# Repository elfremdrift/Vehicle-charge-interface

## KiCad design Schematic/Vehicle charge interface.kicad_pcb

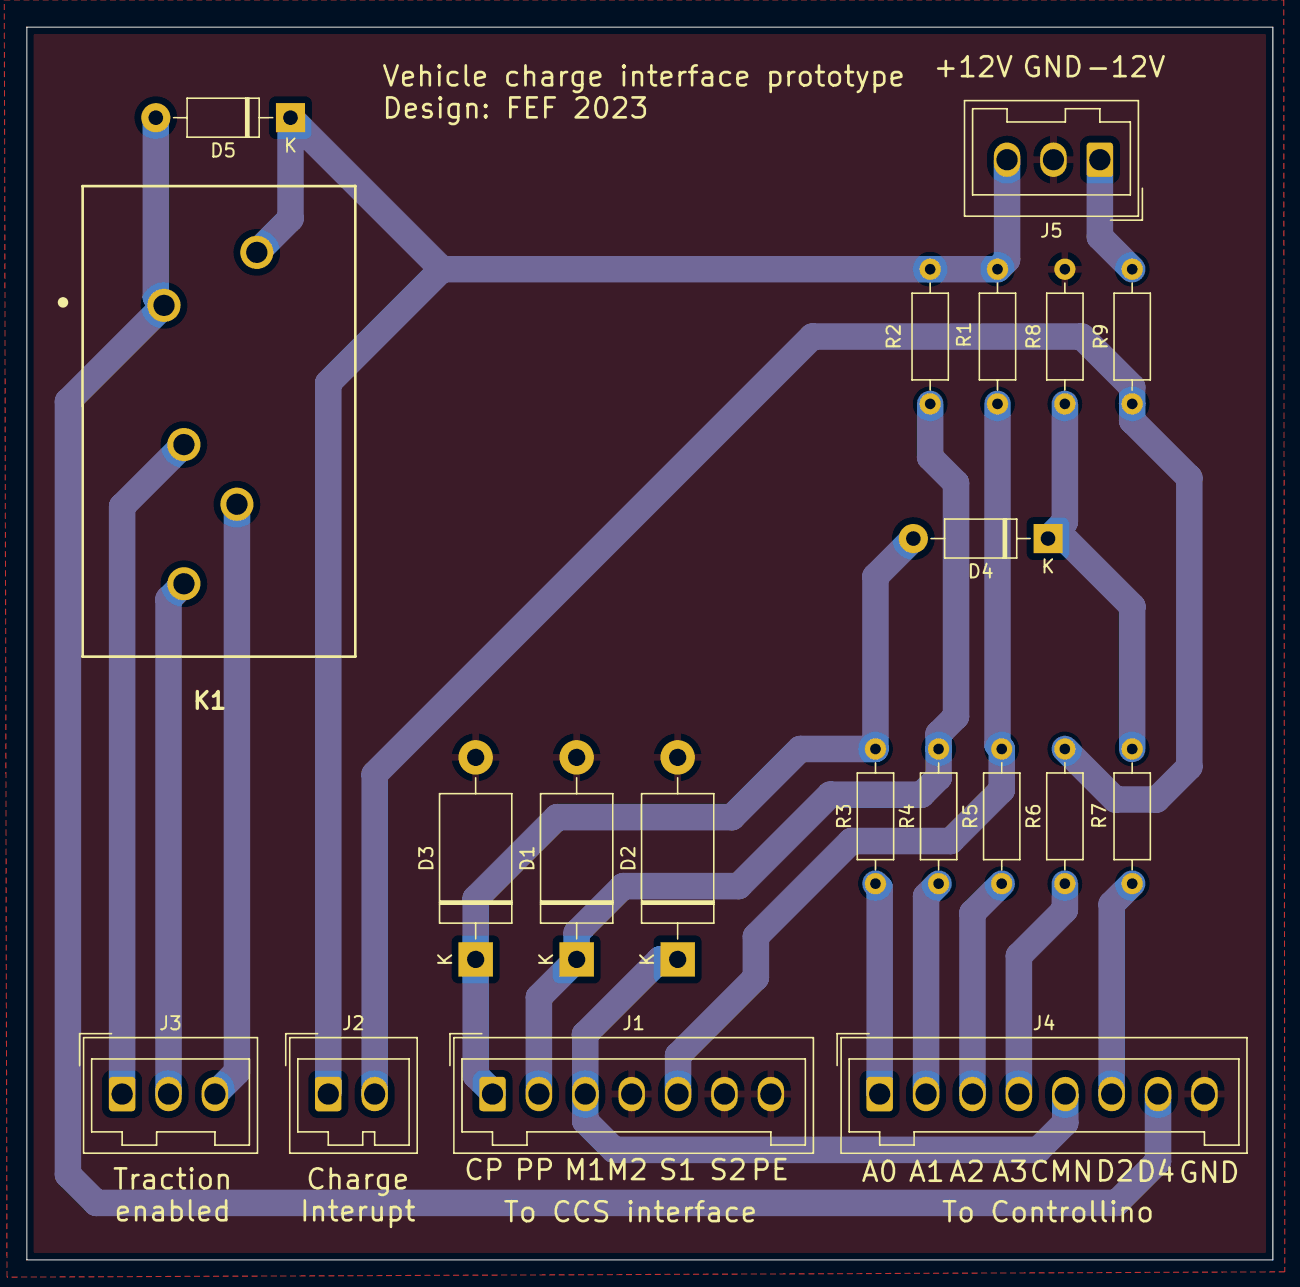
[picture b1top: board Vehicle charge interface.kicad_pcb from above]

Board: 2 copper layers, 94.0 x 93.0 mm, 20 parts (0 on the bottom side), 18 nets.

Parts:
D1, D2, D3: ICTE12C-E3/54; D_DO-201_P15.24mm_Horizontal
D4, D5: 1n4007; D_DO-41_SOD81_P10.16mm_Horizontal
J1: Type 2 lock; Wago_734-137_1x07_P3.50mm_Vertical
J2: Stop charge switch; Wago_734-132_1x02_P3.50mm_Vertical
J3: Traction enable; Wago_734-133_1x03_P3.50mm_Vertical
J4: To Controllino; Wago_734-138_1x08_P3.50mm_Vertical
J5: Power in; Wago_734-133_1x03_P3.50mm_Vertical
K1: OMRON_P2R-05P; P2R-05P
R1: 3k3; R_Axial_DIN0207_L6.3mm_D2.5mm_P10.16mm_Horizontal
R2, R3, R4, R5, R6, R9: 1k; R_Axial_DIN0207_L6.3mm_D2.5mm_P10.16mm_Horizontal
R7: 1k3; R_Axial_DIN0207_L6.3mm_D2.5mm_P10.16mm_Horizontal
R8: 2k7; R_Axial_DIN0207_L6.3mm_D2.5mm_P10.16mm_Horizontal

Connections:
+12V: D5.1 (K), J2.1, J5.3, K1.5, R1.1, R2.1
-12V: J5.1, R9.2
/A0: J4.1, R3.1
/A1: J4.2, R4.1
/A2: J4.3, R5.1
/A3: J4.4, R6.1
/CMN: D2.1 (A1), J1.3, J4.5
/CP: D3.1 (A1), D4.2 (A), J1.1, R3.2
/D2: J4.6, R7.2
/D4: D5.2 (A), J4.7, K1.1
/PP: D1.1 (A1), J1.2, R2.2, R4.2
/S1: J1.5, R1.2, R5.2
GND: D1.2 (A2), D2.2 (A2), D3.2 (A2), J1.4, J1.6, J1.7, J4.8, J5.2, R8.2
unnamed: D4.1 (K), R7.1, R8.1
unnamed: J2.2, R6.2, R9.1
unnamed: J3.1, K1.2
unnamed: J3.2, K1.3
unnamed: J3.3, K1.4

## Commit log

2022-11-16 Added standard library
2022-11-16 Added controller to schematics
2022-11-23 Main parts of schematics added
2022-11-29 Finished most of schematics
2022-11-29 Removed reference to library submodule
2022-11-29 Added local symbol library table
2022-11-29 Added PDF-version of schematic
2022-11-29 Added stop switch
2022-12-04 Setting up directory structure
2022-12-04 Added yEd state diagram
2022-12-06 Initial arduino sketch with a bit of AD support
2022-12-07 Initial state table
2022-12-07 Added timer functions
2022-12-09 Added timer setup for CP measurement
2022-12-10 Timer and AD now working together to measure all values
2022-12-10 Added definitions for processed input values
2022-12-11 Added input filter class
2022-12-12 Update input filters with measured values
2022-12-12 Type fix
2022-12-12 Added spreadsheet with AD threshold value calculations
2022-12-12 Change S1 pullup (R1) to 3k3
2022-12-12 Added state processing and setting output values
2022-12-13 Build fixes
2022-12-13 Added state debug output
2022-12-13 First working version of software :)
2022-12-14 Move state table to PROGMEM
2022-12-14 Add flashing lights
2022-12-14 Fixes after test
2022-12-21 Added "cannot lock" explicit error state w/red flash
2022-12-21 Replaced controllino with connectors to prepare for PCB
2022-12-28 Wider tolerances for AD measurements; avoid unlock loop
2023-01-04 Initial PCB layout
2023-02-01 Singlesided layout - upgraded to KiCad 6
2023-03-01 Renamed software to firmware
2023-03-01 Fix hanging yellow lamp after failed plug insertion
2023-09-24 Added separate wiring diagram
2023-09-24 Added better state debug output
